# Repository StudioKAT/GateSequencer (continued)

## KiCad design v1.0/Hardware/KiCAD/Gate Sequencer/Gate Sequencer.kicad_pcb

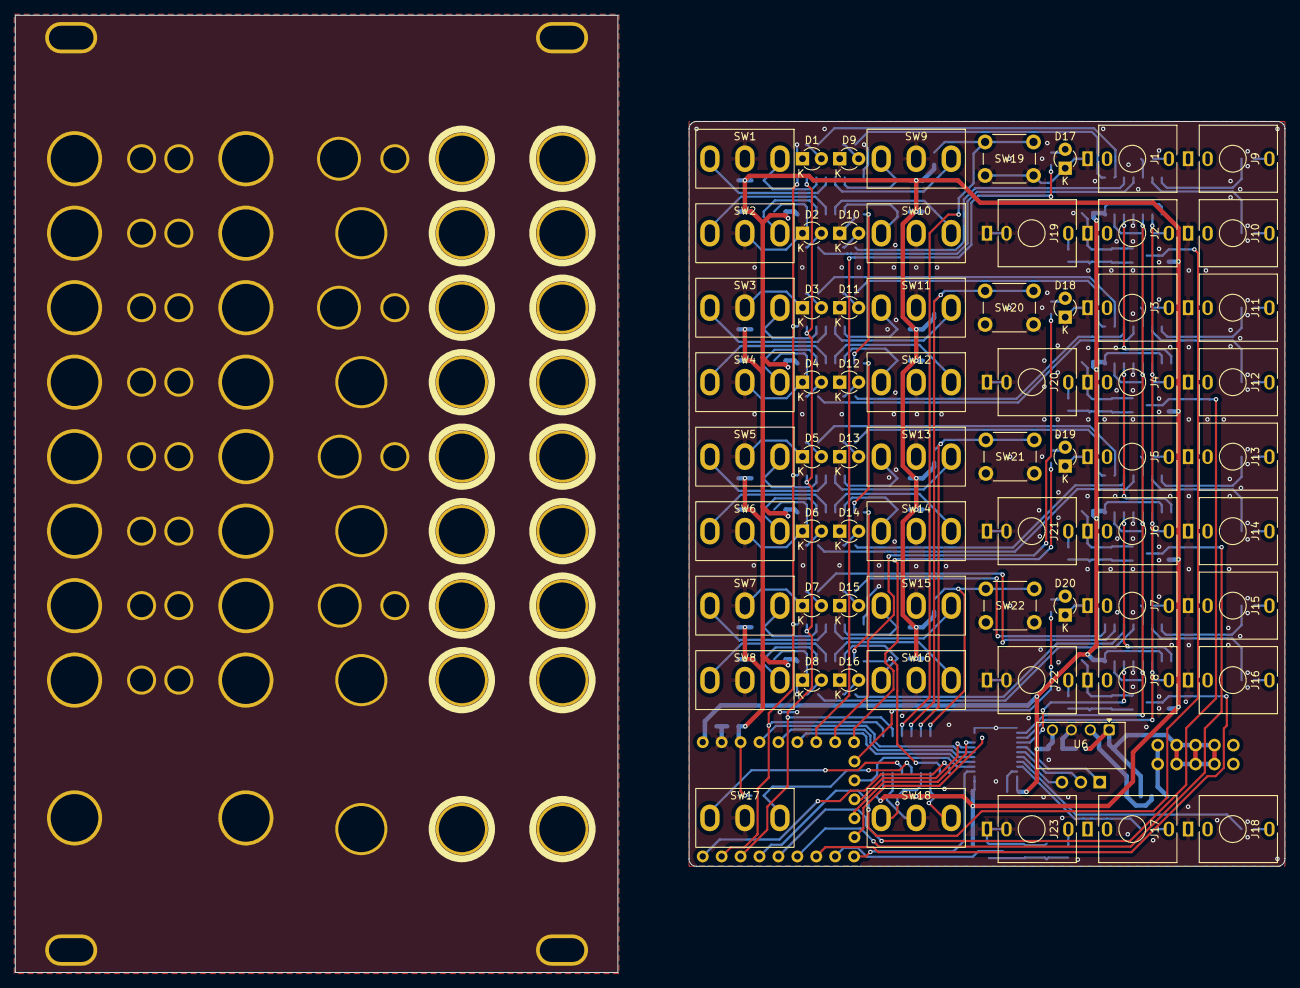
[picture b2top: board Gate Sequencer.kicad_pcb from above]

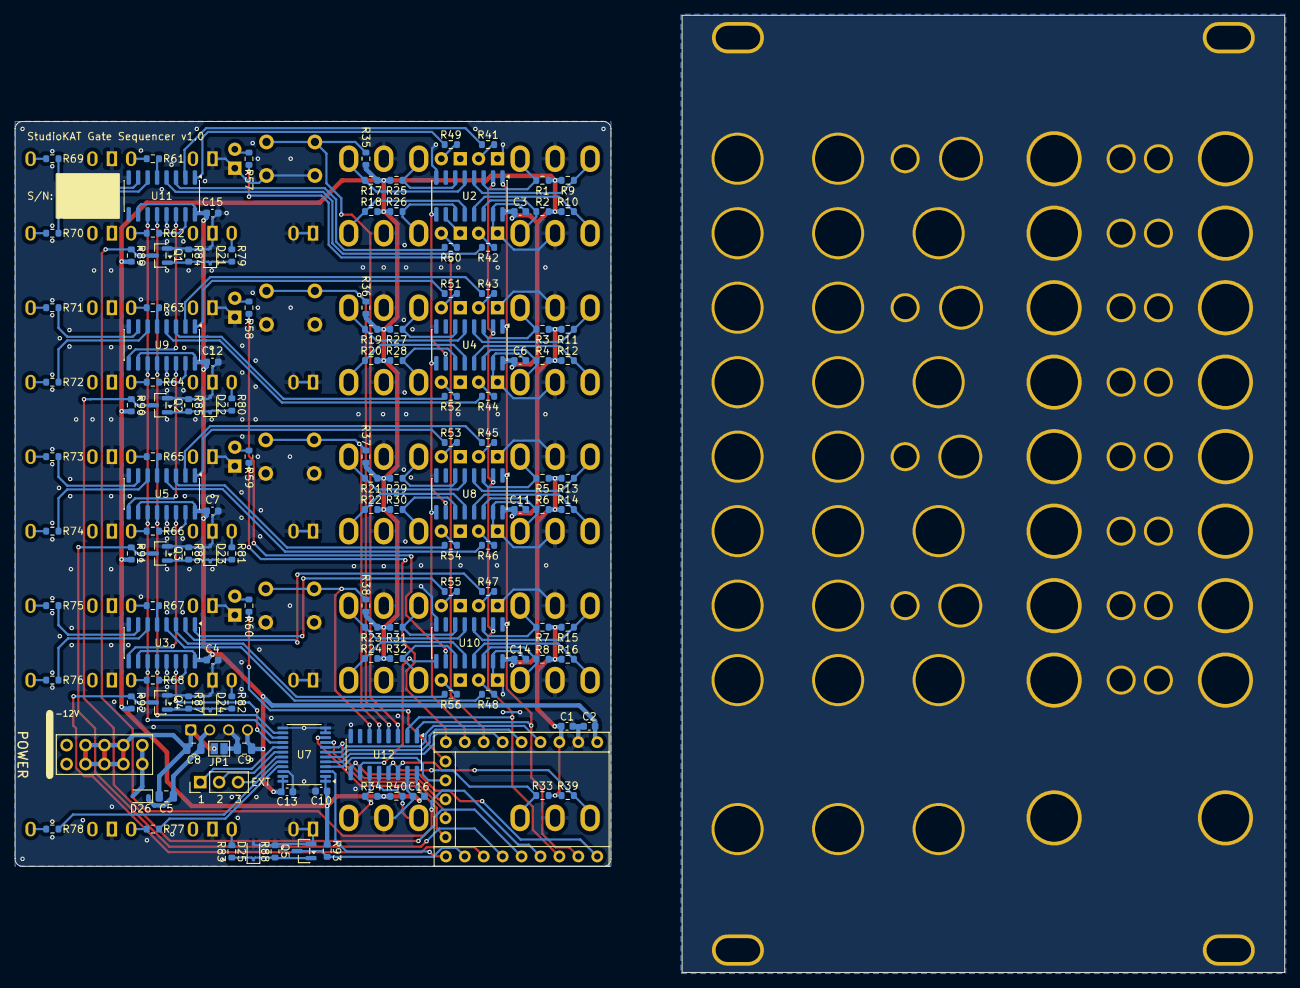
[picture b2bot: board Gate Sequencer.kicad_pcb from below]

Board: 2 copper layers, 170.4 x 128.5 mm, 266 parts (134 on the bottom side), 162 nets.

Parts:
C1, C2, C3, C4, C6, C7, C10, C11, C12, C13, C14, C15, C16: 100nF; C_0603_1608Metric
C5: 22uF; C_0805_2012Metric
C8: 2.2uF; C_0805_2012Metric
C9: 10uF; C_0805_2012Metric
D1, D2, D3, D4, D5, D6, D7, D8, D9, D10, D11, D12, D13, D14, D15, D16, D17, D18, D19, D20: LED; LED_D3.0mm_2hp
D21, D22, D23, D24, D25: 1N4148WS; D_SOD-323
D26: 1N5819WS; D_SOD-323
H1: Panel_16HP
H2, H3, H4, H5, H6, H7, H8, H9, H10, H11, H12, H13, H14, H15, H16, H17, H18, H19, H20, H21, H22, H23, H24: PH_Audio; PH_AudioJack_3.5mm_Pad
H25, H26, H27, H28, H29, H30, H31, H32, H33, H34, H35, H36, H37, H38, H39, H40, H41, H42, H43, H44: PH_LED; PH_LED_3.0mm_Pad
H45, H46, H47, H48, H49, H50, H51, H52, H53, H54, H55, H56, H57, H58, H59, H60, H61, H62: PH_TSW; PH_ToggleSwitch_6.4mm_Pad
H63, H64, H65, H66: PH_PSW; PH_ToggleSwitch_5.1mm_Pad
J1: OUT_1; AudioJack_PJ301M-12
J2: OUT_2; AudioJack_PJ301M-12
J3: OUT_3; AudioJack_PJ301M-12
J4: OUT_4; AudioJack_PJ301M-12
J5: OUT_5; AudioJack_PJ301M-12
J6: OUT_6; AudioJack_PJ301M-12
J7: OUT_7; AudioJack_PJ301M-12
J8: OUT_8; AudioJack_PJ301M-12
J9: OUT_9; AudioJack_PJ301M-12
J10: OUT_10; AudioJack_PJ301M-12
J11: OUT_11; AudioJack_PJ301M-12
J12: OUT_12; AudioJack_PJ301M-12
J13: OUT_13; AudioJack_PJ301M-12
J14: OUT_14; AudioJack_PJ301M-12
J15: OUT_15; AudioJack_PJ301M-12
J16: OUT_16; AudioJack_PJ301M-12
J17: OUT_A; AudioJack_PJ301M-12
J18: OUT_B; AudioJack_PJ301M-12
J19: CLK_A; AudioJack_PJ301M-12
J20: CLK_B; AudioJack_PJ301M-12
J21: RST_A; AudioJack_PJ301M-12
J22: RST_B; AudioJack_PJ301M-12
J23: PAUSE; AudioJack_PJ301M-12
J24: POWER; BoxHeader_2x05_2.54mm_Europower
J25: EXT; PinHeader_1x03_P2.54mm_Vertical
JP1: Jumper_2_Open; SolderJumper-2_P1.3mm_Open_Pad1.0x1.5mm
Q1, Q2, Q3, Q4, Q5: MMBT3904; SOT-23
R1, R2, R3, R4, R5, R6, R7, R8, R9, R10, R11, R12, R13, R14, R15, R16, R17, R18, R19, R20, R21, R22, R23, R24, R25, R26, R27, R28, R29, R30, R31, R32, R33, R34, R35, R36, R37, R38, R39, R40, R89, R90, R91, R92, R93: 10K; R_0603_1608Metric
R41, R42, R43, R44, R45, R46, R47, R48, R49, R50, R51, R52, R53, R54, R55, R56: 2.4K; R_0603_1608Metric
R57, R58, R59, R60, R61, R62, R63, R64, R65, R66, R67, R68, R69, R70, R71, R72, R73, R74, R75, R76, R77, R78: 1K; R_0603_1608Metric
R79, R80, R81, R82, R83, R84, R85, R86, R87, R88: 100K; R_0603_1608Metric
SW1, SW2, SW3, SW4, SW5, SW6, SW7, SW8, SW9, SW10, SW11, SW12, SW13, SW14, SW15, SW16, SW17, SW18: MTS-103; SW_MTS-102_103
SW19, SW20, SW21, SW22: SW_Push; SW_PUSH_6mm_H13mm
U1: RP2040-Zero
U2, U4, U8, U10, U12: 74HC165D,653; SOIC-16_3.9x9.9mm_P1.27mm
U3, U5, U9, U11: 74HC595D,118; SOIC-16_3.9x9.9mm_P1.27mm
U6: B1205S-1WR3; Converter_DCDC_TRACO_TEA1-xxxx_THT
U7: SN74LVC4245APWR; TSSOP-24_4.4x7.8mm_P0.65mm

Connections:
+3.3V: C1.1, C3.2, C6.2, C10.2, C11.2, C14.2, C16.2, R1.1, R2.1, R3.1, R4.1, R5.1, R6.1, R7.1, R8.1, R9.1, R10.1, R11.1, R12.1, R13.1, R14.1, R15.1, R16.1, R17.1, R18.1, R19.1, R20.1, R21.1, R22.1, R23.1, R24.1, R25.1, R26.1, R27.1, R28.1, R29.1, R30.1, R31.1, R32.1, R33.1, R34.1, R35.1, R36.1, R37.1, R38.1, R39.1, R40.1, R89.1, R90.1, R91.1, R92.1, R93.1, U1.30 (3V3), U2.16 (VCC), U4.16 (VCC), U7.1 (VCCA), U7.2 (DIR), U8.16 (VCC), U10.16 (VCC), U12.16 (VCC)
+5V: C2.2, C4.2, C7.2, C9.1, C12.2, C13.1, C15.2, U1.32 (5V), U3.10 (~SRCLR), U3.16 (VCC), U5.10 (~SRCLR), U5.16 (VCC), U6.4 (+Vout), U7.23 (VCCB), U7.24 (VCCB), U9.10 (~SRCLR), U9.16 (VCC), U11.10 (~SRCLR), U11.16 (VCC)
+12V: C5.1, C8.1, D26.1 (K), U6.2 (+Vin)
/CLK_A: Q1.3 (C), R89.2, U1.3
/CLK_B: Q2.3 (C), R90.2, U1.4
/Clock: U1.2, U2.2 (CP), U4.2 (CP), U8.2 (CP), U10.2 (CP), U12.2 (CP)
/LED_1: R41.1, U11.2 (QC)
/LED_2: R42.1, U11.4 (QE)
/LED_3: R43.1, U9.2 (QC)
/LED_4: R44.1, U9.4 (QE)
/LED_5: R45.1, U5.2 (QC)
/LED_6: R46.1, U5.4 (QE)
/LED_7: R47.1, U3.2 (QC)
/LED_8: R48.1, U3.4 (QE)
/LED_9: R49.1, U11.1 (QB)
/LED_10: R50.1, U11.3 (QD)
/LED_11: R51.1, U9.1 (QB)
/LED_12: R52.1, U9.3 (QD)
/LED_13: R53.1, U5.1 (QB)
/LED_14: R54.1, U5.3 (QD)
/LED_15: R55.1, U3.1 (QB)
/LED_16: R56.1, U3.3 (QD)
/LED_A: R57.1, U1.26
/LED_B: R58.1, U1.15
/LED_C: R59.1, U1.14
/LED_D: R60.1, U1.13
/OUT_1: R61.1, U11.5 (QF)
/OUT_2: R62.1, U11.15 (QA)
/OUT_3: R63.1, U9.5 (QF)
/OUT_4: R64.1, U9.15 (QA)
/OUT_5: R65.1, U5.5 (QF)
/OUT_6: R66.1, U5.15 (QA)
/OUT_7: R67.1, U3.5 (QF)
/OUT_8: R68.1, U3.15 (QA)
/OUT_9: R69.1, U11.7 (QH)
/OUT_10: R70.1, U11.6 (QG)
/OUT_11: R71.1, U9.7 (QH)
/OUT_12: R72.1, U9.6 (QG)
/OUT_13: R73.1, U5.7 (QH)
/OUT_14: R74.1, U5.6 (QG)
/OUT_15: R75.1, U3.7 (QH)
/OUT_16: R76.1, U3.6 (QG)
/OUT_A: R77.1, U7.21 (B1)
/OUT_B: R78.1, U7.20 (B2)
/PAUSE: Q5.3 (C), R93.2, U1.7
/RCLK: U3.12 (RCLK), U5.12 (RCLK), U7.14 (B8), U9.12 (RCLK), U11.12 (RCLK)
/RP2040_EXT_1: U1.29, U7.7 (A5)
/RP2040_EXT_2: U1.28, U7.6 (A4)
/RP2040_EXT_3: U1.27, U7.5 (A3)
/RP2040_OUT_A: U1.8, U7.3 (A1)
/RP2040_OUT_B: U1.12, U7.4 (A2)
/RP2040_RCLK: U1.9, U7.10 (A8)
/RP2040_SER: U1.11, U7.8 (A6)
/RP2040_SRCLK: U1.10, U7.9 (A7)
/RST_A: Q3.3 (C), R91.2, U1.5
/RST_B: Q4.3 (C), R92.2, U1.6
/SER: U3.14 (SER), U7.16 (B6)
/SRCLK: U3.11 (SRCLK), U5.11 (SRCLK), U7.15 (B7), U9.11 (SRCLK), U11.11 (SRCLK)
/SR_Read: U1.0, U12.9 (Q7)
/SW_1_A: R1.2, SW1.1, U2.3 (D4)
/SW_1_B: R9.2, SW1.3 (4), U2.4 (D5)
/SW_2_A: R2.2, SW2.1, U2.14 (D3)
/SW_2_B: R10.2, SW2.3 (4), U2.13 (D2)
/SW_3_A: R3.2, SW3.1, U4.3 (D4)
/SW_3_B: R11.2, SW3.3 (4), U4.4 (D5)
/SW_4_A: R4.2, SW4.1, U4.14 (D3)
/SW_4_B: R12.2, SW4.3 (4), U4.13 (D2)
/SW_5_A: R5.2, SW5.1, U8.3 (D4)
/SW_5_B: R13.2, SW5.3 (4), U8.4 (D5)
/SW_6_A: R6.2, SW6.1, U8.14 (D3)
/SW_6_B: R14.2, SW6.3 (4), U8.13 (D2)
/SW_7_A: R7.2, SW7.1, U10.3 (D4)
/SW_7_B: R15.2, SW7.3 (4), U10.4 (D5)
/SW_8_A: R8.2, SW8.1, U10.14 (D3)
/SW_8_B: R16.2, SW8.3 (4), U10.13 (D2)
/SW_9_A: R17.2, SW9.1, U2.5 (D6)
/SW_9_B: R25.2, SW9.3 (4), U2.6 (D7)
/SW_10_A: R18.2, SW10.1, U2.12 (D1)
/SW_10_B: R26.2, SW10.3 (4), U2.11 (D0)
/SW_11_A: R19.2, SW11.1, U4.5 (D6)
/SW_11_B: R27.2, SW11.3 (4), U4.6 (D7)
/SW_12_A: R20.2, SW12.1, U4.12 (D1)
/SW_12_B: R28.2, SW12.3 (4), U4.11 (D0)
/SW_13_A: R21.2, SW13.1, U8.5 (D6)
/SW_13_B: R29.2, SW13.3 (4), U8.6 (D7)
/SW_14_A: R22.2, SW14.1, U8.12 (D1)
/SW_14_B: R30.2, SW14.3 (4), U8.11 (D0)
/SW_15_A: R23.2, SW15.1, U10.5 (D6)
/SW_15_B: R31.2, SW15.3 (4), U10.6 (D7)
/SW_16_A: R24.2, SW16.1, U10.12 (D1)
/SW_16_B: R32.2, SW16.3 (4), U10.11 (D0)
/SW_17_A: R33.2, SW17.1, U12.13 (D2)
/SW_17_B: R39.2, SW17.3 (4), U12.14 (D3)
/SW_18_A: R34.2, SW18.1, U12.11 (D0)
/SW_18_B: R40.2, SW18.3 (4), U12.12 (D1)
/SW_Push_1: R35.2, SW19.1, U12.3 (D4)
/SW_Push_2: R36.2, SW20.1, U12.4 (D5)
/SW_Push_3: R37.2, SW21.1, U12.5 (D6)
/SW_Push_4: R38.2, SW22.1, U12.6 (D7)
/Shift/nLoad: U1.1, U2.1 (~PL), U4.1 (~PL), U8.1 (~PL), U10.1 (~PL), U12.1 (~PL)
GND: C1.2, C2.1, C3.1, C4.1, C6.1, C7.1, C9.2, C10.1, C11.1, C12.1, C13.2, C14.1, C15.1, C16.1, D1.1 (K), D2.1 (K), D3.1 (K), D4.1 (K), D5.1 (K), D6.1 (K), D7.1 (K), D8.1 (K), D9.1 (K), D10.1 (K), D11.1 (K), D12.1 (K), D13.1 (K), D14.1 (K), D15.1 (K), D16.1 (K), D17.1 (K), D18.1 (K), D19.1 (K), D20.1 (K), D21.2 (A), D22.2 (A), D23.2 (A), D24.2 (A), D25.2 (A), J1.S, J2.S, J3.S, J4.S, J5.S, J6.S, J7.S, J8.S, J9.S, J10.S, J11.S, J12.S, J13.S, J14.S, J15.S, J16.S, J17.S, J18.S, J19.S, J19.TN, J20.S, J20.TN, J21.S, J21.TN, J22.S, J22.TN, J23.S, J23.TN, JP1.2 (B), Q1.2 (E), Q2.2 (E), Q3.2 (E), Q4.2 (E), Q5.2 (E), R84.2, R85.2, R86.2, R87.2, R88.2, SW1.2 (3), SW2.2 (3), SW3.2 (3), SW4.2 (3), SW5.2 (3), SW6.2 (3), SW7.2 (3), SW8.2 (3), SW9.2 (3), SW10.2 (3), SW11.2 (3), SW12.2 (3), SW13.2 (3), SW14.2 (3), SW15.2 (3), SW16.2 (3), SW17.2 (3), SW18.2 (3), SW19.2, SW20.2, SW21.2, SW22.2, U1.31 (GND), U2.8 (GND), U2.10 (DS), U2.15 (~CE), U3.8 (GND), U3.13 (~OE), U4.8 (GND), U4.15 (~CE), U5.8 (GND), U5.13 (~OE), U6.3 (-Vout), U7.11 (GND), U7.12 (GND), U7.13 (GND), U7.22 (~OE), U8.8 (GND), U8.15 (~CE), U9.8 (GND), U9.13 (~OE), U10.8 (GND), U10.15 (~CE), U11.8 (GND), U11.13 (~OE), U12.8 (GND), U12.15 (~CE)
GND1: C5.2, C8.2, J24.3, J24.4, J24.5, J24.6, J24.7, J24.8, JP1.1 (A), U6.1 (-Vin)
GND2: H1.1, H2.1, H3.1, H4.1, H5.1, H6.1, H7.1, H8.1, H9.1, H10.1, H11.1, H12.1, H13.1, H14.1, H15.1, H16.1, H17.1, H18.1, H19.1, H20.1, H21.1, H22.1, H23.1, H24.1, H25.1, H26.1, H27.1, H28.1, H29.1, H30.1, H31.1, H32.1, H33.1, H34.1, H35.1, H36.1, H37.1, H38.1, H39.1, H40.1, H41.1, H42.1, H43.1, H44.1, H45.1, H46.1, H47.1, H48.1, H49.1, H50.1, H51.1, H52.1, H53.1, H54.1, H55.1, H56.1, H57.1, H58.1, H59.1, H60.1, H61.1, H62.1, H63.1, H64.1, H65.1, H66.1
unnamed: D1.2 (A), R41.2
unnamed: D2.2 (A), R42.2
unnamed: D3.2 (A), R43.2
unnamed: D4.2 (A), R44.2
unnamed: D5.2 (A), R45.2
unnamed: D6.2 (A), R46.2
unnamed: D7.2 (A), R47.2
unnamed: D8.2 (A), R48.2
unnamed: D9.2 (A), R49.2
unnamed: D10.2 (A), R50.2
unnamed: D11.2 (A), R51.2
unnamed: D12.2 (A), R52.2
unnamed: D13.2 (A), R53.2
unnamed: D14.2 (A), R54.2
unnamed: D15.2 (A), R55.2
unnamed: D16.2 (A), R56.2
unnamed: D17.2 (A), R57.2
unnamed: D18.2 (A), R58.2
unnamed: D19.2 (A), R59.2
unnamed: D20.2 (A), R60.2
unnamed: D21.1 (K), Q1.1 (B), R79.2, R84.1
unnamed: D22.1 (K), Q2.1 (B), R80.2, R85.1
unnamed: D23.1 (K), Q3.1 (B), R81.2, R86.1
unnamed: D24.1 (K), Q4.1 (B), R82.2, R87.1
unnamed: D25.1 (K), Q5.1 (B), R83.2, R88.1
unnamed: D26.2 (A), J24.1, J24.2
unnamed: J1.T, R61.2
unnamed: J2.T, R62.2
unnamed: J3.T, R63.2
unnamed: J4.T, R64.2
unnamed: J5.T, R65.2
unnamed: J6.T, R66.2
unnamed: J7.T, R67.2
unnamed: J8.T, R68.2
unnamed: J9.T, R69.2
unnamed: J10.T, R70.2
unnamed: J11.T, R71.2
unnamed: J12.T, R72.2
unnamed: J13.T, R73.2
unnamed: J14.T, R74.2
unnamed: J15.T, R75.2
unnamed: J16.T, R76.2
unnamed: J17.T, R77.2
unnamed: J18.T, R78.2
unnamed: J19.T, R79.1
unnamed: J20.T, R80.1
unnamed: J21.T, R81.1
unnamed: J22.T, R82.1
unnamed: J23.T, R83.1
unnamed: J25.1, U7.17 (B5)
unnamed: J25.2, U7.18 (B4)
unnamed: J25.3, U7.19 (B3)
unnamed: U2.9 (Q7), U4.10 (DS)
unnamed: U3.9 (QH'), U5.14 (SER)
unnamed: U4.9 (Q7), U8.10 (DS)
unnamed: U5.9 (QH'), U9.14 (SER)
unnamed: U8.9 (Q7), U10.10 (DS)
unnamed: U10.9 (Q7), U12.10 (DS)
unnamed: U9.9 (QH'), U11.14 (SER)

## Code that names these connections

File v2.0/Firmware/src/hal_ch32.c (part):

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 * ピン割り当て
 * --------------------------------------------------------- */
// 直結入力（トランジスタで反転 → ソフトで再反転して正論理にする）
#define PIN_IN_CLK    PD0  // EXTI0
#define PIN_IN_PAUSE  PA1  // EXTI1
#define PIN_IN_A      PD2  // EXTI2
#define PIN_IN_B      PD3  // EXTI3
#define PIN_IN_C      PD4  // EXTI4

// SPI1: 595 と 165 で SCK を共用
#define PIN_SPI_SCK   PC5
#define PIN_SPI_MOSI  PC6  // 595 SER
#define PIN_SPI_MISO  PC7  // 165 Q7
#define PIN_595_RCLK  PC1
#define PIN_165_SH_LD PC2  // LOW でパラレルロード

// TRIG 出力
#define PIN_TRIG_A    PC3
#define PIN_TRIG_B    PC4

// 乱数シード用 ADC（PA2 = A0、未接続）
#define ADC_CH_SEED   0
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  funDigitalWrite(PIN_165_SH_LD, FUN_HIGH);

  RCC->APB2PCENR |= RCC_APB2Periph_SPI1;
  funPinMode(PIN_SPI_SCK,  GPIO_Speed_50MHz | GPIO_CNF_OUT_PP_AF);
  funPinMode(PIN_SPI_MOSI, GPIO_Speed_50MHz | GPIO_CNF_OUT_PP_AF);
  funPinMode(PIN_SPI_MISO, GPIO_CFGLR_IN_FLOAT);

  // Mode 0（CPOL=0, CPHA=1Edge）・MSB first・48MHz/8 = 6MHz
  SPI1->CTLR1 = 0;
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
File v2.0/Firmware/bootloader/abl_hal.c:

// オーディオブートローダのハード層（CH32V003 / ch32fun）
// ピンの正本: docs/hardware.md。595 / 165 の手順は src/hal_ch32.c と同じ
#include "ch32fun.h"
#include "abl_hal.h"
#include "io_map.h"

// PAUSE 入力 = PA1（トランジスタで反転）、SPI1 SCK / MOSI / MISO = PC5 / PC6 / PC7
#define PIN_595_RCLK  PC1
#define PIN_165_SH_LD PC2

#define FLASH_BASE_ADDR 0x08000000u

static uint8_t s_in165[IO_FRAME_BYTES];

// GPIOC の設定（1 ピン 4bit、PC7..PC0）。1920B に収めるため funPinMode を使わず一度に書く
//   PC7 MISO 入力 / PC6 MOSI・PC5 SCK 代替機能 50MHz / PC4・PC3（TRIG）・PC0 入力（リセット後と同じ）
//   PC2 SH/LD・PC1 RCLK 出力 10MHz
#define CFG_IN   0x4u
#define CFG_OUT  (GPIO_Speed_10MHz | GPIO_CNF_OUT_PP)
#define CFG_AF   (GPIO_Speed_50MHz | GPIO_CNF_OUT_PP_AF)
#define GPIOC_CFG ((CFG_IN << 28) | (CFG_AF << 24) | (CFG_AF << 20) | (CFG_IN << 16) \
                 | (CFG_IN << 12) | (CFG_OUT << 8) | (CFG_OUT << 4) | CFG_IN)

void ablHalInit(void)
{
  // PA1（PAUSE 入力）はリセット後の入力（フローティング）のまま使う。外部 12kΩ で 5V にプルアップ済み
  RCC->APB2PCENR |= RCC_APB2Periph_GPIOA | RCC_APB2Periph_GPIOC | RCC_APB2Periph_SPI1;
  GPIOC->BSHR = (1u << 2) | (1u << (16 + 1)); // SH/LD = HIGH、RCLK = LOW から始める
  GPIOC->CFGLR = GPIOC_CFG;
  SPI1->CTLR1 = SPI_CPHA_1Edge | SPI_CPOL_Low | SPI_Mode_Master | SPI_NSS_Soft
              | SPI_BaudRatePrescaler_8 | SPI_DataSize_8b | SPI_Direction_2Lines_FullDuplex;
  SPI1->CTLR1 |= CTLR1_SPE_Set;
}

void ablHalLeds(uint16_t leds, uint8_t panel)
{
  // ioBuildOutFrame は表が大きいので、ステップ LED のビット位置の表で 1 個ずつ立てる（ゲート出力は常に LOW）
  uint8_t out[IO_FRAME_BYTES] = { ioPanelFrameByte(panel), 0, 0, 0, 0 };
  for (uint8_t ch = 0; ch < 16; ++ch) {
    const uint8_t pos = IO_STEP_LED_BIT[ch];
    if (leds & (1u << ch)) out[pos >> 3] |= (uint8_t)(1u << (pos & 7u));
  }
  // 165 のロード・595 のラッチのパルスは、GPIO への 2 回の書き込みの間隔（24MHz で 1 クロック以上、約 42ns）で
  // 足りる（74HC165 / 595 の要求は 5V で約 20ns）。本体の hal_ch32.c にある nop は 1920B に収めるため省く
  funDigitalWrite(PIN_165_SH_LD, FUN_LOW);
  funDigitalWrite(PIN_165_SH_LD, FUN_HIGH);
  for (uint8_t i = 0; i < IO_FRAME_BYTES; ++i) {
    while (!(SPI1->STATR & SPI_STATR_TXE)) {}
    SPI1->DATAR = out[i];
    while (!(SPI1->STATR & SPI_STATR_RXNE)) {}
    s_in165[i] = (uint8_t)SPI1->DATAR;
  }
  while (SPI1->STATR & SPI_STATR_BSY) {}
  funDigitalWrite(PIN_595_RCLK, FUN_HIGH);
  funDigitalWrite(PIN_595_RCLK, FUN_LOW);
}

bool ablHalPushAB(void)
{
  return ioDecodePush(s_in165, PUSH_A) && ioDecodePush(s_in165, PUSH_B);
}

uint32_t ablHalTicks(void) { return SysTick->CNT; }

bool ablHalPause(void) { return !(GPIOA->INDR & (1u << 1)); } // PA1、トランジスタの反転を戻す

/* ---------------------------------------------------------
 * Flash
 * --------------------------------------------------------- */

const uint8_t *ablHalFlash(void) { return (const uint8_t *)FLASH_BASE_ADDR; }

void ablHalFlashUnlock(void)
{
  FLASH->KEYR = FLASH_KEY1;
  FLASH->KEYR = FLASH_KEY2;
  FLASH->MODEKEYR = FLASH_KEY1; // 64B ページの高速消去・書き込み
  FLASH->MODEKEYR = FLASH_KEY2;
}

static void waitBusy(void) { while (FLASH->STATR & FLASH_STATR_BSY) {} }

void ablHalErasePage(uint32_t offset)
{
  FLASH->CTLR = CR_PAGE_ER;
  FLASH->ADDR = FLASH_BASE_ADDR + offset;
  FLASH->CTLR = CR_STRT_Set | CR_PAGE_ER;
  waitBusy();
}

// 消去してから 64B を書く（ch32fun examples/flashtest と同じ手順）
void ablHalWritePage(uint32_t offset, const uint8_t *data)
{
  ablHalErasePage(offset);
  volatile uint32_t *p = (volatile uint32_t *)(FLASH_BASE_ADDR + offset);
  FLASH->CTLR = CR_PAGE_PG;
  FLASH->CTLR = CR_BUF_RST | CR_PAGE_PG;
  FLASH->ADDR = FLASH_BASE_ADDR + offset;
  waitBusy();
  for (uint8_t i = 0; i < ABL_PAGE_SIZE / 4u; ++i) {
    const uint8_t *d = &data[i * 4u]; // パケットのバッファは 4B 境界にないのでバイトで組み立てる
    p[i] = (uint32_t)d[0] | (uint32_t)d[1] << 8 | (uint32_t)d[2] << 16 | (uint32_t)d[3] << 24;
    FLASH->CTLR = CR_PAGE_PG | CR_BUF_LOAD;
    waitBusy();
  }
  FLASH->CTLR = CR_PAGE_PG | CR_STRT_Set;
  waitBusy();
}

// ch32fun examples/bootload と同じ手順。キーを書く前に必ずロックしておく
// （アンロック済みでキーを書き直すと、STM32 系の仕様では誤った順序とみなされるため。書き込みモードから来る場合）
void ablHalBootApp(void)
{
  FLASH->CTLR = CR_LOCK_Set;
  FLASH->KEYR = FLASH_KEY1;
  FLASH->KEYR = FLASH_KEY2;
  FLASH->BOOT_MODEKEYR = FLASH_KEY1;
  FLASH->BOOT_MODEKEYR = FLASH_KEY2;
  FLASH->STATR = 0; // MODE（bit14）= 0: 次のリセットでユーザー領域から起動
  FLASH->CTLR = CR_LOCK_Set;
  PFIC->SCTLR = 1u << 31;
  while (1) {}
}

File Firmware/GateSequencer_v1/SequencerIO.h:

#pragma once
#include <stdint.h>
#include <stdbool.h>

// =============================================================================
// 定数・Enum 定義
// =============================================================================

// Pushボタンのインデックス定義（可読性向上のため）
enum PushIndex {
  PUSH_IDX_CLK = 1, // 旧 Push1: 手動クロック
  PUSH_IDX_A   = 2, // 旧 Push2: IN A 対応
  PUSH_IDX_B   = 3, // 旧 Push3: IN B 対応
  PUSH_IDX_C   = 4  // 旧 Push4: IN C 対応
};

// パネルLEDピン（アプリケーション側からも参照できるようにextern宣言）
extern const uint8_t PIN_PANEL_LED_CLK; // 旧 LED_A
extern const uint8_t PIN_PANEL_LED_A;   // 旧 LED_B
extern const uint8_t PIN_PANEL_LED_B;   // 旧 LED_C
extern const uint8_t PIN_PANEL_LED_C;   // 旧 LED_D

// =============================================================================
// 構造体定義
// =============================================================================

// トリガ最小幅シェーパ用構造体
// 短すぎるトリガ信号を引き延ばして出力するための管理用データ
struct TrigShaper {
  uint32_t minUs;       // 最小パルス幅(µs)
  bool     bypass;      // 入力が高速な場合はシェーピングをバイパスするフラグ
  bool     prevBase;    // 前回の入力レベル
  uint32_t lastRiseUs;  // 直近の立ち上がり時刻
  uint32_t prevRiseUs;  // その一つ前の立ち上がり時刻（周期計測用）
  uint32_t holdUntil;   // 出力をHighに保持する期限時刻
};

// =============================================================================
// 公開関数プロトタイプ
// =============================================================================

// システム初期化・入力ポーリング・PWM駆動
void seqBegin();
void seqPollInputs();      // 入力状態の更新（ループ内で定期的に呼ぶ）
void seqPwmService();      // PWM更新用（互換性のために残存、現在はタイマ駆動）

// スイッチ / Pushボタン 読み取り
//   seqReadSwitch: 1..18 → 0(下) / 1(中) / 2(上)
//   seqReadPush  : PushIndex または 1..4 → 押下中ならtrue
uint8_t seqReadSwitch(uint8_t idx1to18);
bool    seqReadPush(uint8_t idx1to4);

// 高速ゲート入力：現在の信号レベル取得
bool seqReadClkIn();
bool seqReadAIn();
bool seqReadBIn();
bool seqReadCIn();
bool seqReadPauseIn();

// 高速ゲート入力：エッジ検出（読み出し時にカウンタをクリアして返す）
// 割り込みでカウントしているため、極めて短いパルスも取りこぼさない
uint32_t seqTakeAndClearClkInRise();
uint32_t seqTakeAndClearClkInFall();
uint32_t seqTakeAndClearAInRise();
uint32_t seqTakeAndClearAInFall();
uint32_t seqTakeAndClearBInRise();
uint32_t seqTakeAndClearBInFall();
uint32_t seqTakeAndClearCInRise();
uint32_t seqTakeAndClearCInFall();
uint32_t seqTakeAndClearPauseRise();
uint32_t seqTakeAndClearPauseFall();

// OUT (Gate) 出力制御
void seqSetOutMask(uint16_t mask);         // 16bit一括設定
void seqGateWrite(uint8_t ch, bool level); // 個別チャンネル設定 (ch: 1..16)
void seqGateWriteMask(uint16_t mask);      // seqSetOutMaskのエイリアス
void seqAllGatesOff();                     // 全ゲートOFF

// TRIG 出力制御 (直結ピン)
void seqTrigA(bool level);
void seqTrigB(bool level);

// ステップLED制御 (ch:1..16, pct:0..100)
// PWM制御により輝度調整が可能
void seqLedSetPct(uint8_t ch, uint8_t pct);
void seqLedSetOffAll();

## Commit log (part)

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2025-11-27 Firmware v1 プロジェクト名変更
2025-11-27 Firmware v2.0 Update
2025-11-29 Firmware v2.1 Update
2025-11-29 ディレクトリ構造変更
